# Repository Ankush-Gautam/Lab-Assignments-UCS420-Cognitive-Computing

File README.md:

# Assignments
Name: Ankush Gautam Roll: 102316016 Batch: 2P11

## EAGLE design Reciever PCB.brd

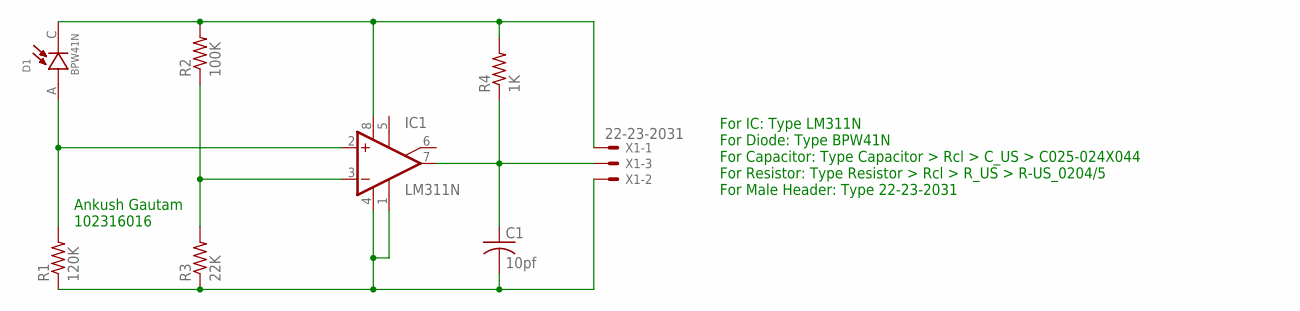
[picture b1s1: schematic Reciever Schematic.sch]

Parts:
C1: 10pf; C025-025X050
D1: BPW41N; DIO_BPW41N
IC1: LM311N; DIL08
R1: 120K; 0204/5
R2: 100K; 0204/5
R3: 22K; 0204/5
R4: 1K; 0204/5
X1: 22-23-2031

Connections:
unnamed: D1.A, IC1.2 (+IN), R1.2
unnamed: C1.2, IC1.1 (GND), IC1.4 (V-), R1.1, R3.1, X1.2
unnamed: D1.C, IC1.8 (V+), R2.2, R4.2, X1.1
unnamed: IC1.3 (-IN), R2.1, R3.2
unnamed: C1.1, IC1.7 (OUT), R4.1, X1.3

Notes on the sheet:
Ankush Gautam 102316016
For IC: Type LM311N For Diode: Type BPW41N For Capacitor: Type Capacitor > Rcl > C_US > C025-024X044 For Resistor: Type Resistor > Rcl > R_US > R-US_0204/5 For Male Header: Type 22-23-2031

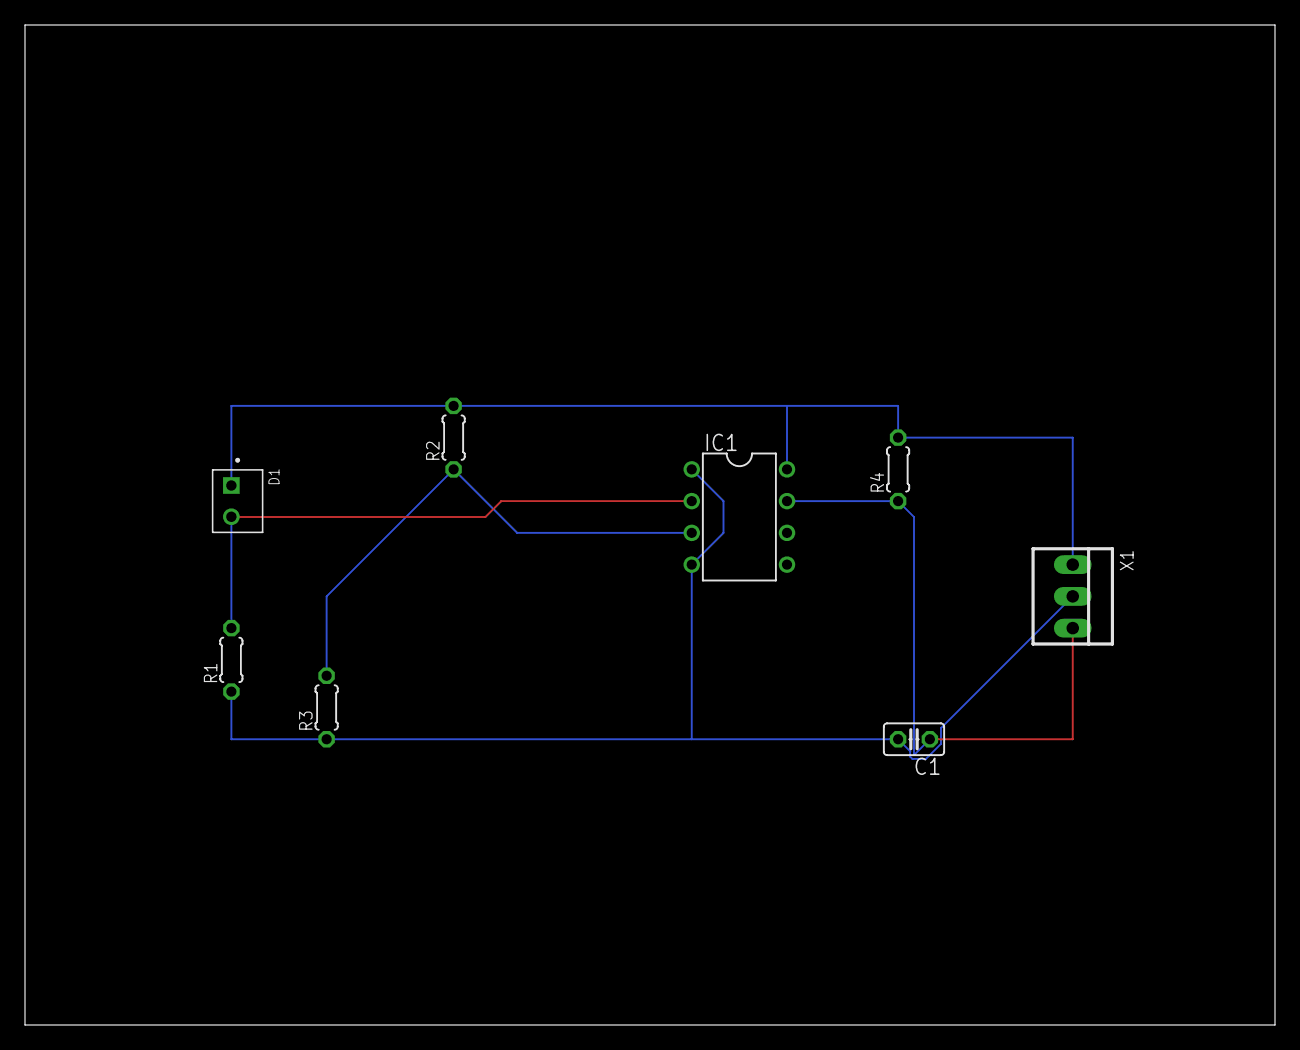
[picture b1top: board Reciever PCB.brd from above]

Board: 2 copper layers, 100.0 x 80.0 mm, 8 parts (0 on the bottom side), 5 nets.

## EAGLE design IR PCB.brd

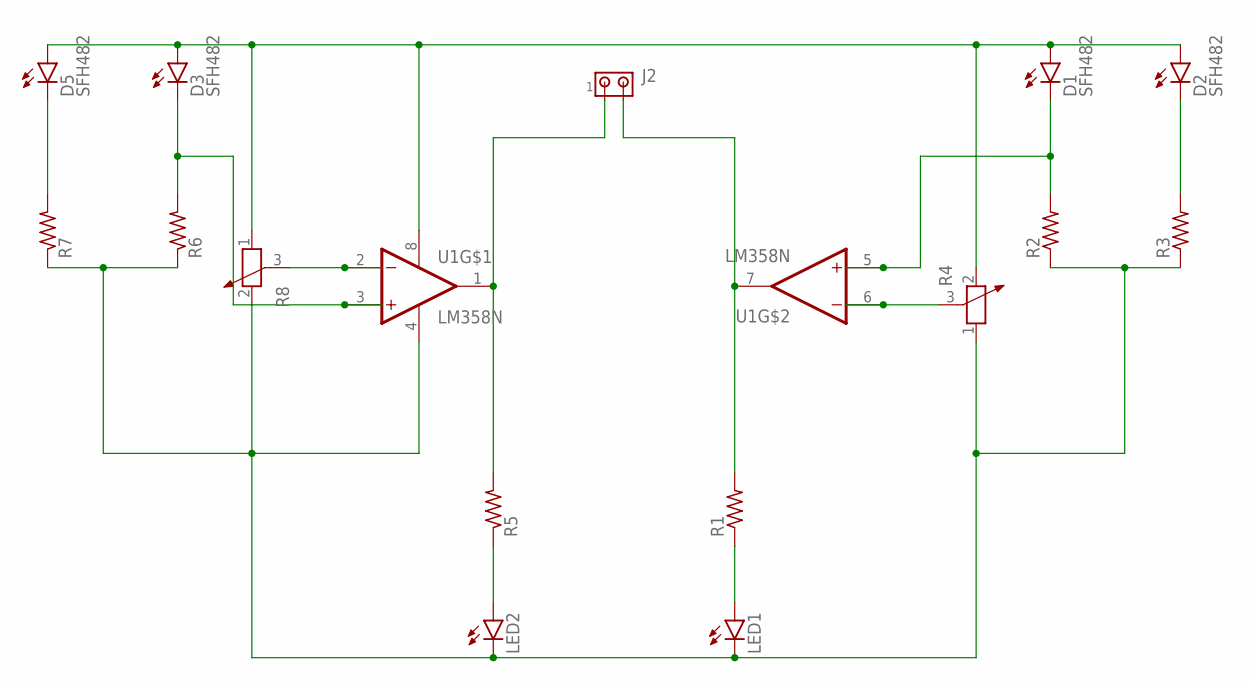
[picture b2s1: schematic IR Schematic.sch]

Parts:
D1, D2, D3, D5: SFH482
J2: MTA02-100; 10X02MTA
LED1, LED2: LED3MM
R1, R2, R3, R5, R6, R7: R-US_0204/5; 0204/5
R4, R8: POTENTIOMETER_PT-10; PT-10
U1: LM358N; DIP762W46P254L960H508Q8

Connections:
unnamed: R4.3, U1.6 (2IN-)
unnamed: J2.2, R1.2, U1.7 (2OUT)
unnamed: D3.K (C), R6.2, U1.3 (1IN+)
unnamed: LED1.A, R1.1
unnamed: D2.K (C), R3.2
unnamed: D1.K (C), R2.2, U1.5 (2IN+)
unnamed: R8.3, U1.2 (1IN-)
unnamed: J2.1, R5.2, U1.1 (1OUT)
unnamed: LED2.A, R5.1
unnamed: LED1.K (C), LED2.K (C), R2.1, R3.1, R4.1, R6.1, R7.1, R8.2, U1.4 (GND)
unnamed: D1.A, D2.A, D3.A, D5.A, R4.2, R8.1, U1.8 (VCC)
unnamed: D5.K (C), R7.2

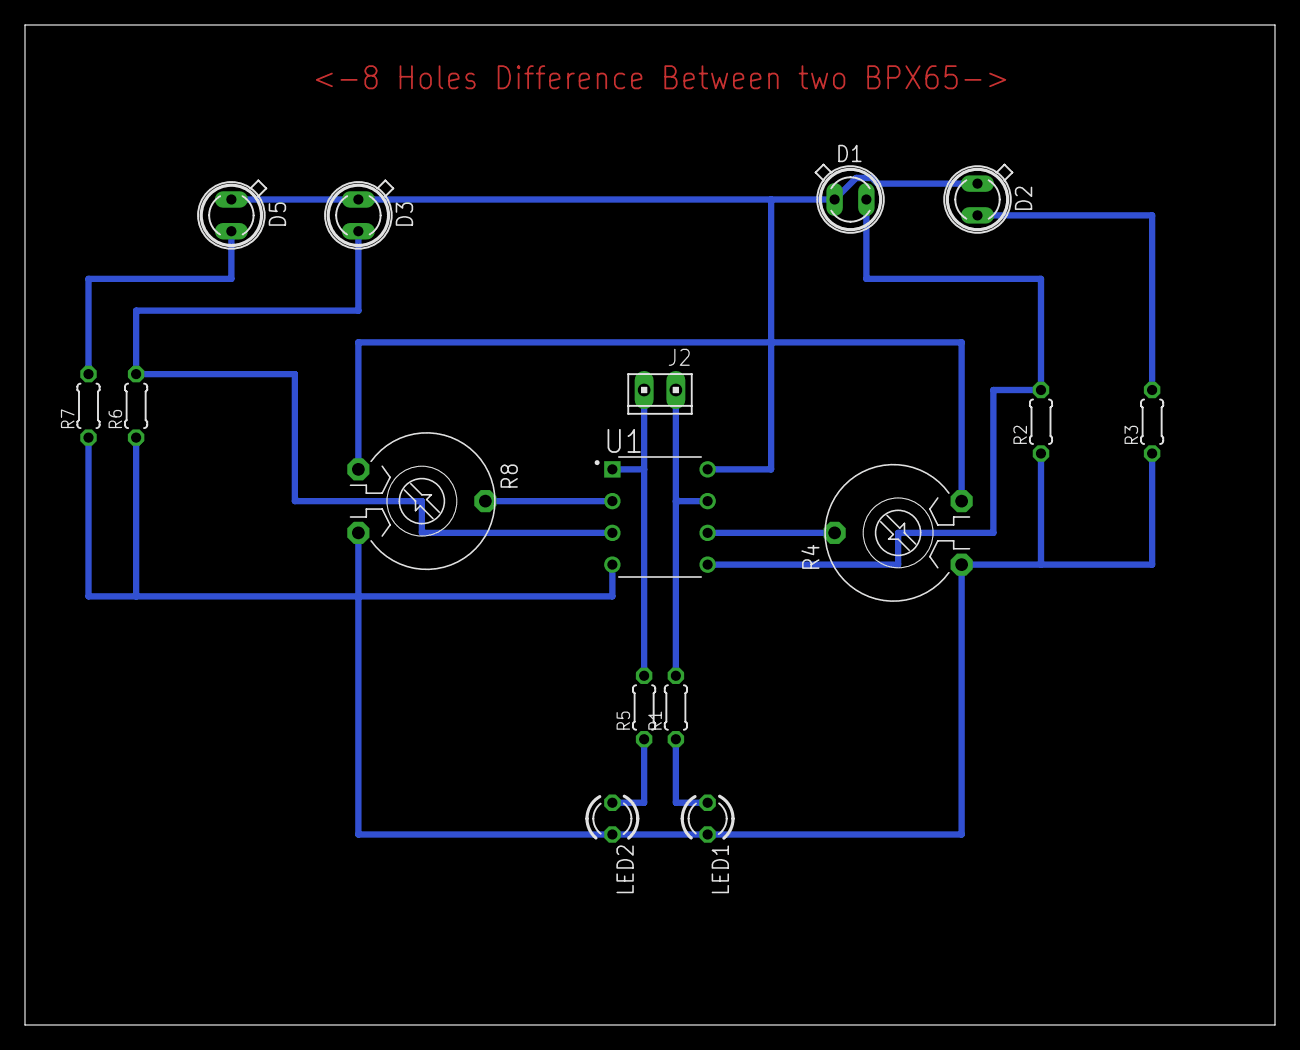
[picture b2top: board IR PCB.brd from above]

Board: 2 copper layers, 100.0 x 80.0 mm, 16 parts (0 on the bottom side), 12 nets.

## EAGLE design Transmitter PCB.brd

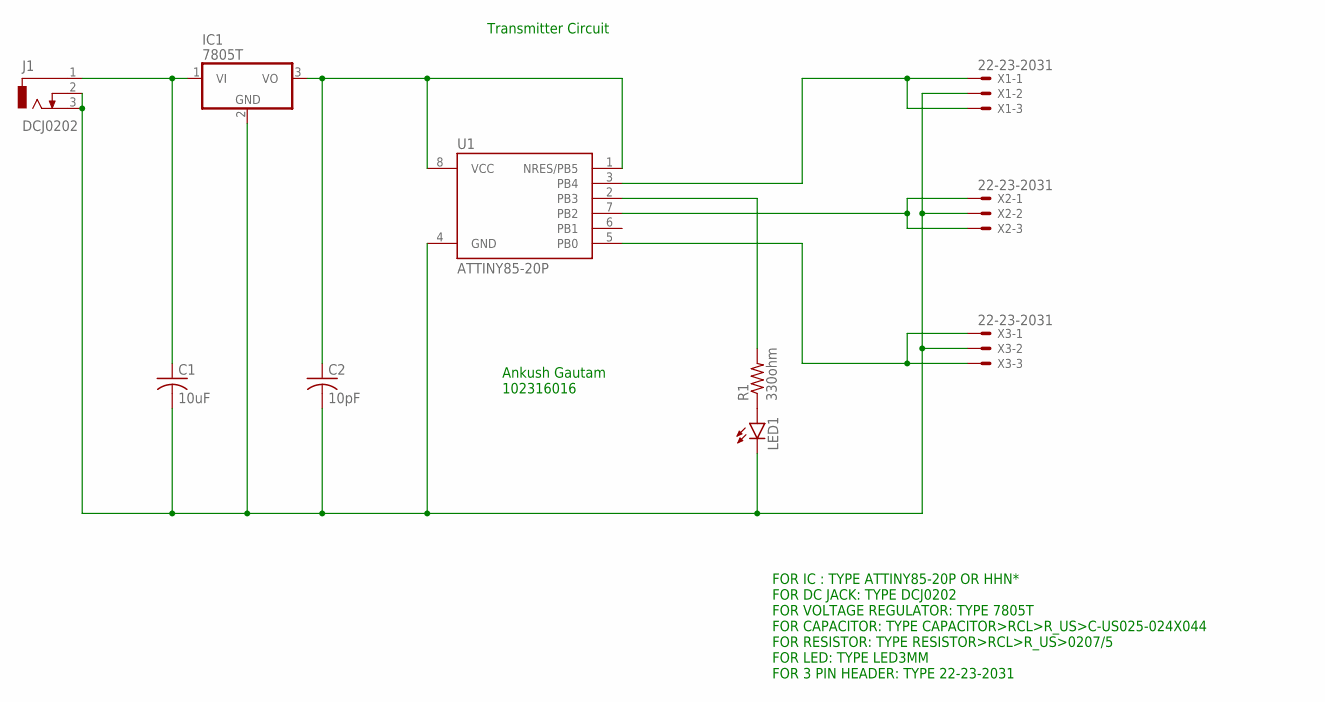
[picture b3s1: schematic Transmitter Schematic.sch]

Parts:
C1: 10uF; C025-024X044
C2: 10pF; C025-024X044
IC1: 7805T; TO220H
J1: DCJ0202
LED1: LED3MM
R1: 330ohm; 0204/5
U1: ATTINY85-20P; PDIP08_300MIL
X1, X2, X3: 22-23-2031

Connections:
unnamed: C1.1, IC1.1 (VI), J1.1
unnamed: C1.2, C2.2, IC1.2 (GND), J1.2, J1.3, LED1.K (C), U1.4 (GND), X1.2, X2.2, X3.2
unnamed: C2.1, IC1.3 (VO), U1.1 (NRES/PB5), U1.8 (VCC)
unnamed: U1.3 (PB4), X1.1, X1.3
unnamed: LED1.A, R1.1
unnamed: U1.7 (PB2), X2.1, X2.3
unnamed: R1.2, U1.2 (PB3)
unnamed: U1.5 (PB0), X3.1, X3.3

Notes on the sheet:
FOR IC : TYPE ATTINY85-20P OR HHN* FOR DC JACK: TYPE DCJ0202 FOR VOLTAGE REGULATOR: TYPE 7805T FOR CAPACITOR: TYPE CAPACITOR>RCL>R_US>C-US025-024X044 FOR RESISTOR: TYPE RESISTOR>RCL>R_US>0207/5 FOR LED: TYPE LED3MM FOR 3 PIN HEADER: TYPE 22-23-2031
Transmitter Circuit
Ankush Gautam 102316016

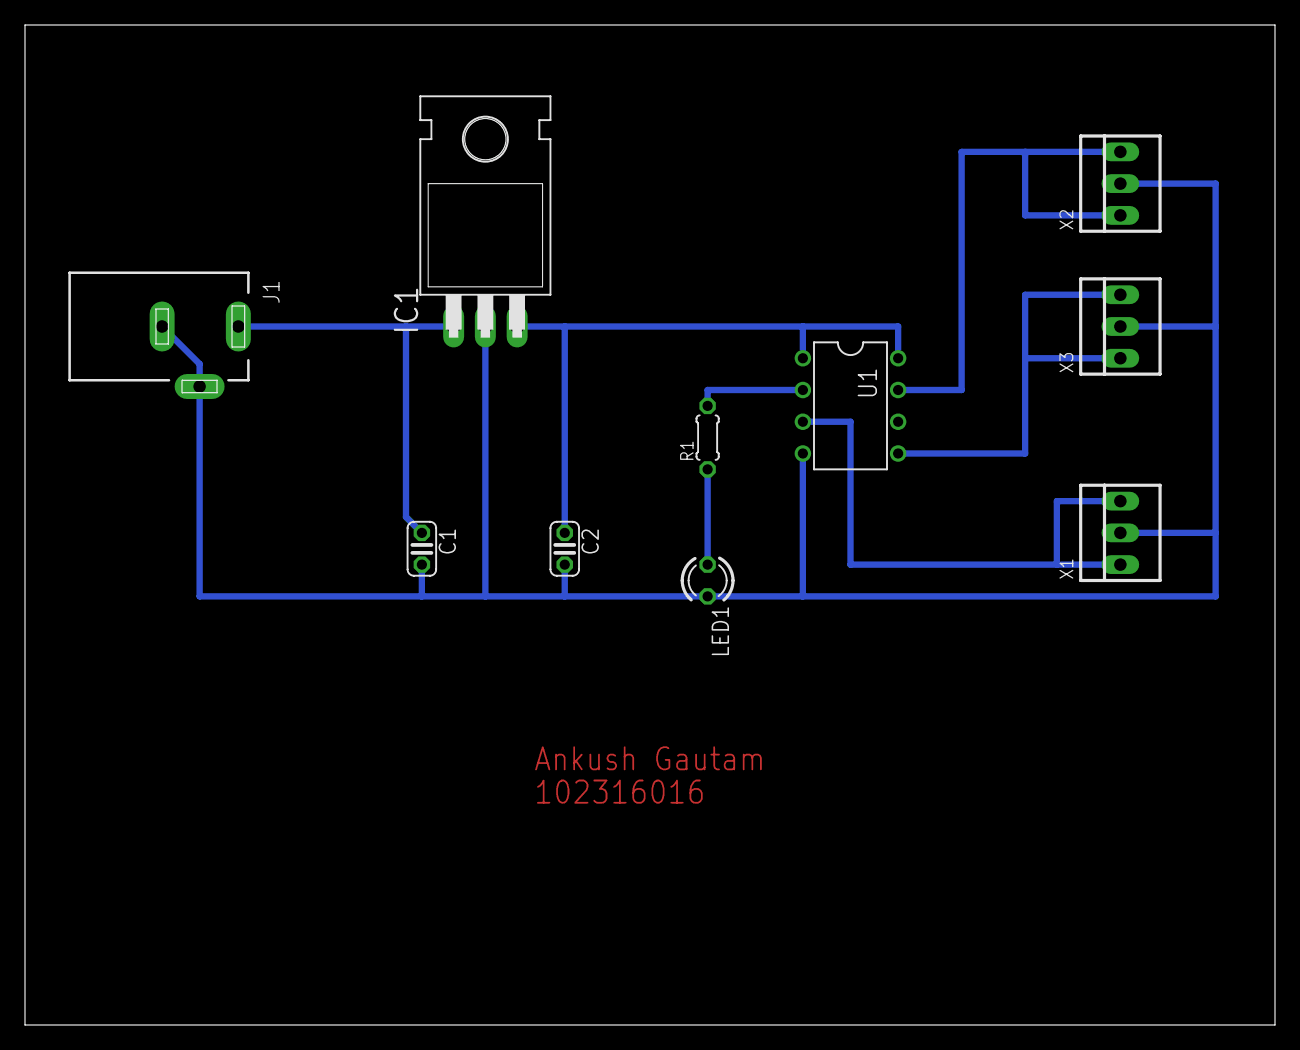
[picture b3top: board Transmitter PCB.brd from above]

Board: 2 copper layers, 100.0 x 80.0 mm, 10 parts (0 on the bottom side), 8 nets.
